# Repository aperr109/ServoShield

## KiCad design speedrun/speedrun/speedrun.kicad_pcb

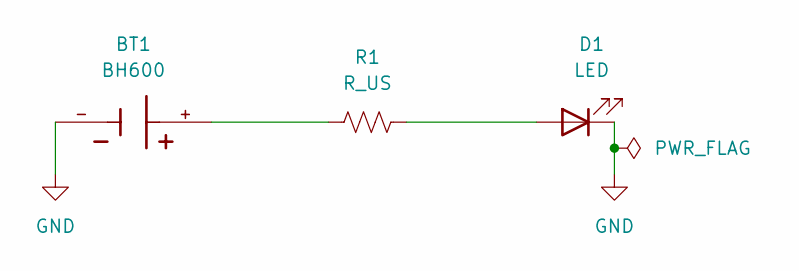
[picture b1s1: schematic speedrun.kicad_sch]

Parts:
BT1: BH600; BAT_BH600; PARTREV D
D1: LED; LED_D1.8mm_W3.3mm_H2.4mm
R1: R_US; R_Axial_DIN0414_L11.9mm_D4.5mm_P15.24mm_Horizontal

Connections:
GND: BT1.-, D1.1 (K)
unnamed: BT1.+, R1.1
unnamed: D1.2 (A), R1.2

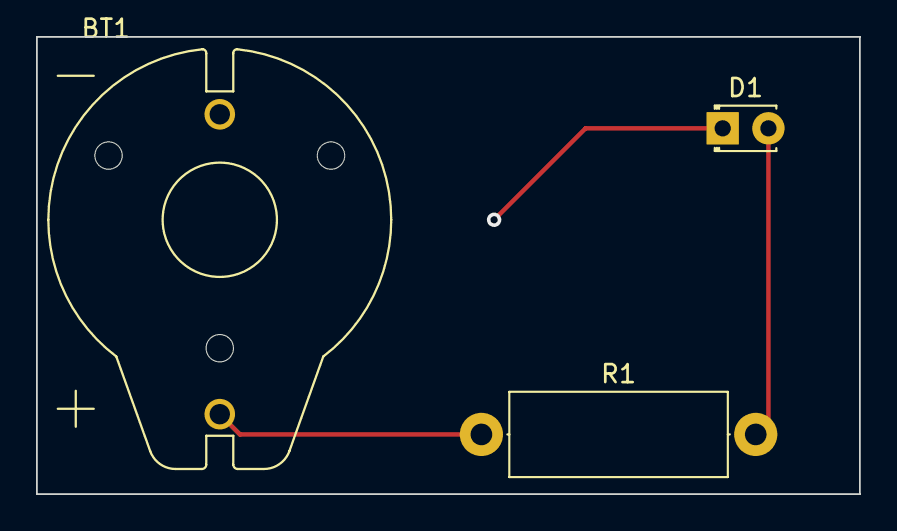
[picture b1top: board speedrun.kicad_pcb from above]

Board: 4 copper layers, 45.7 x 25.4 mm, 3 parts (0 on the bottom side), 3 nets.

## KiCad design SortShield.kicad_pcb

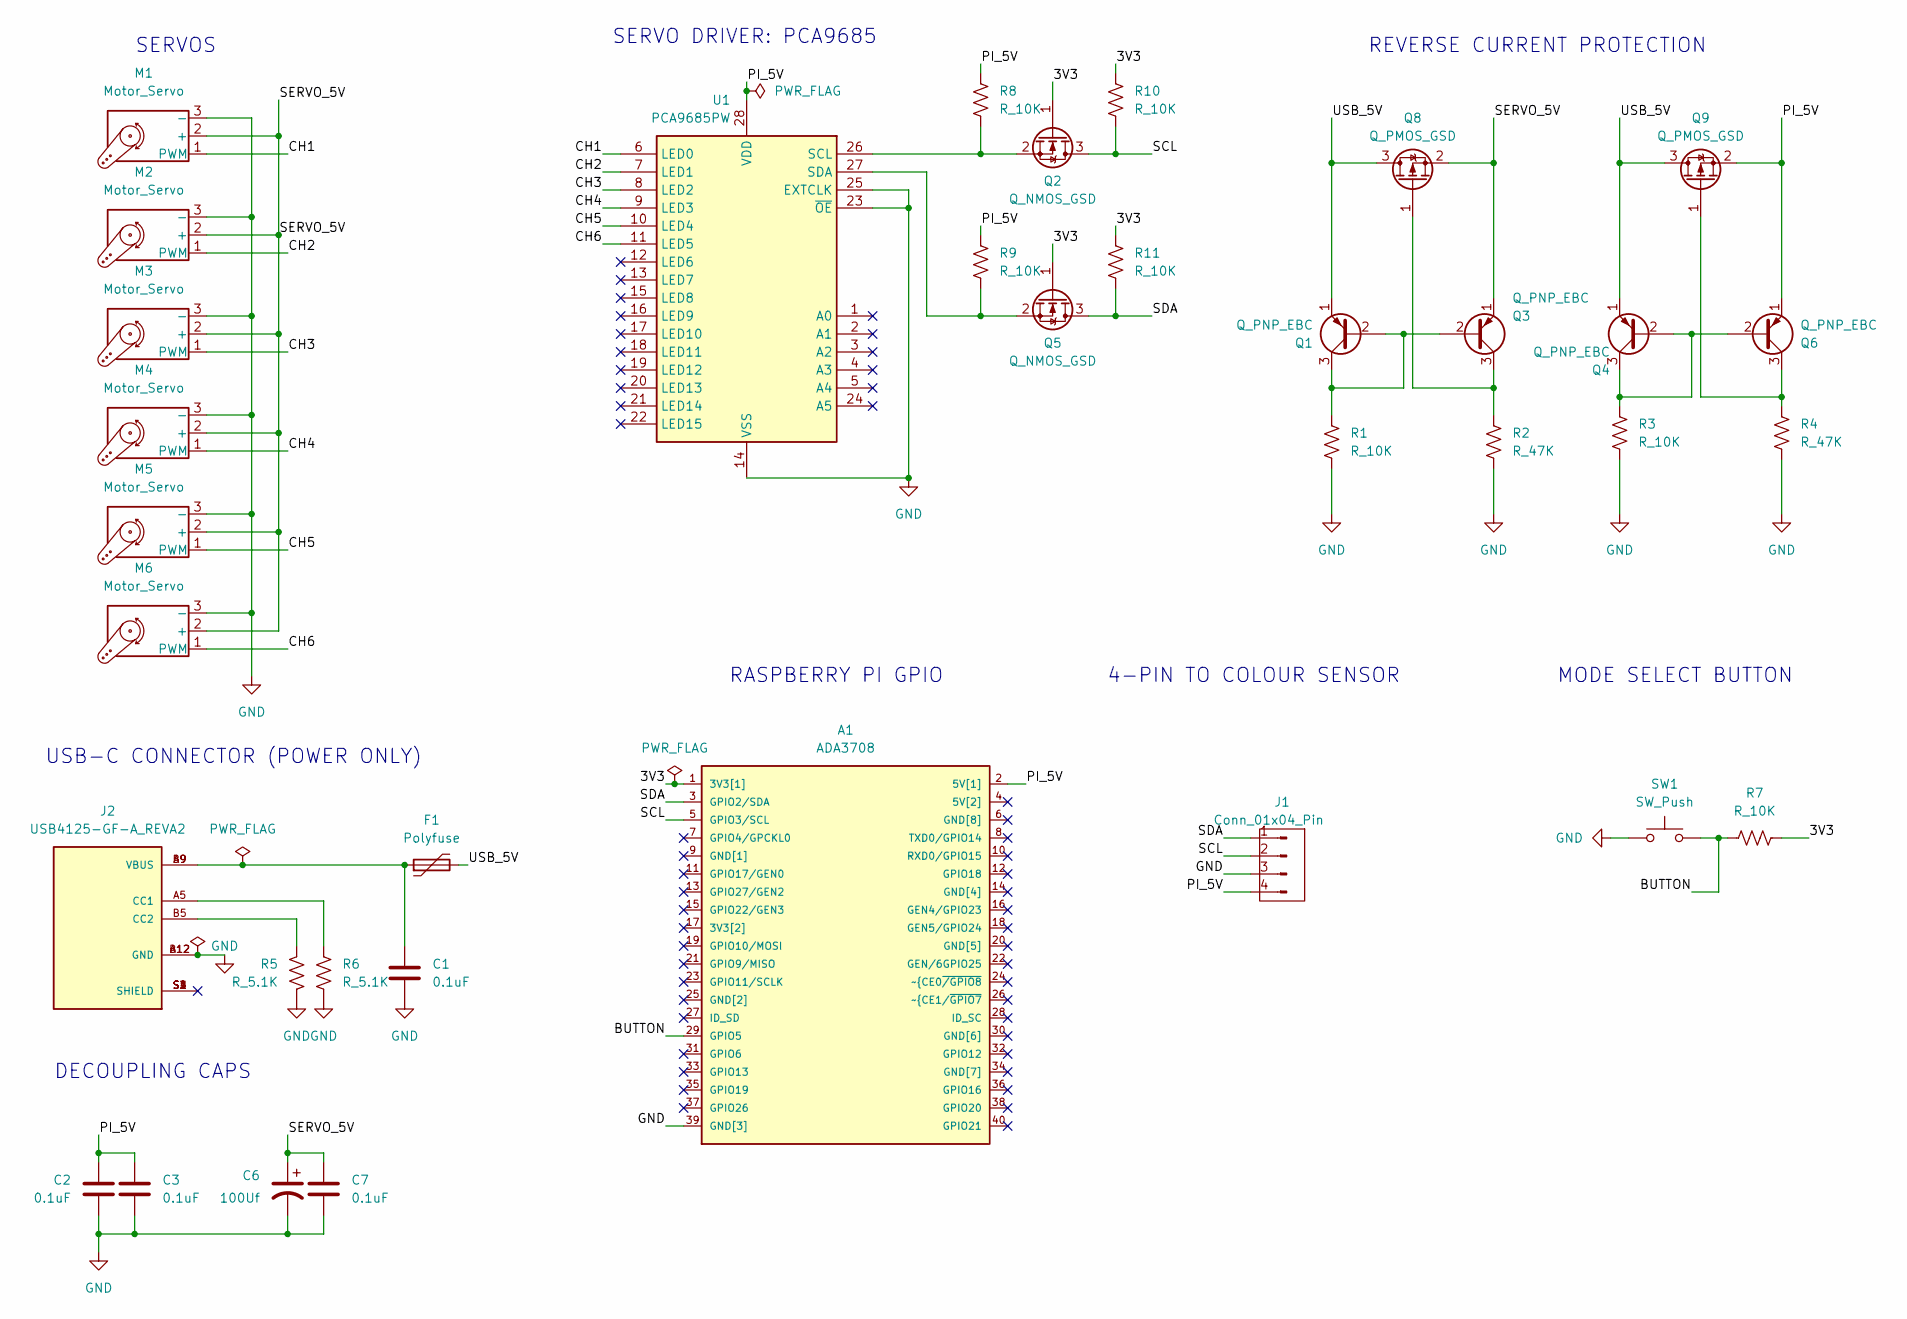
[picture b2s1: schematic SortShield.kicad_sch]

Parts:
A1: ADA3708; ADA3708_RPI-ZERO
C1, C2, C3, C7: 0.1uF; C_0805_2012Metric
C6: 100Uf; CAPAE660X800N
F1: Polyfuse; 6vfuse
J1: Conn_01x04_Pin; PinHeader_1x04_P2.54mm_Vertical
J2: USB4125-GF-A_REVA2; GCT_USB4125-GF-A_REVA2; PARTREV Rev A2
M1, M2, M3, M4, M5, M6: Motor_Servo; PinHeader_1x03_P2.54mm_Vertical
Q1, Q3, Q4, Q6: Q_PNP_EBC; TRANS_MMBT2907A-13
Q2, Q5: Q_NMOS_GSD; SOT91P240X110-3N
Q8, Q9: Q_PMOS_GSD; SSM3J338R,LF
R1, R3, R7, R8, R9, R10, R11: R_10K; R_0805_2012Metric
R2, R4: R_47K; R_0805_2012Metric
R5, R6: R_5.1K; R_0805_2012Metric
SW1: SW_Push; SW_TS04-66-65-BK-160-SMT
U1: PCA9685PW; TSSOP-28_4.4x9.7mm_P0.65mm

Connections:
/3V3: A1.1 (3V3[1]), Q2.1 (G), Q5.1 (G), R7.2, R10.1, R11.1
/BUTTON: A1.29 (GPIO5), R7.1, SW1.2
/CH1: M1.1 (PWM), U1.6 (LED0)
/CH2: M2.1 (PWM), U1.7 (LED1)
/CH3: M3.1 (PWM), U1.8 (LED2)
/CH4: M4.1 (PWM), U1.9 (LED3)
/CH5: M5.1 (PWM), U1.10 (LED4)
/CH6: M6.1 (PWM), U1.11 (LED5)
/PI_5V: A1.2 (5V[1]), C2.1, C3.1, J1.4, Q6.1 (E), Q9.2 (S), R8.1, R9.1, U1.28 (VDD)
/SCL: A1.5 (GPIO3/SCL), J1.2, Q2.3 (D), R10.2
/SDA: A1.3 (GPIO2/SDA), J1.1, Q5.3 (D), R11.2
/SERVO_5V: C6.1, C7.1, M1.2 (+), M2.2 (+), M3.2 (+), M4.2 (+), M5.2 (+), M6.2 (+), Q3.1 (E), Q8.2 (S)
/USB_5V: F1.2, Q1.1 (E), Q4.1 (E), Q8.3 (D), Q9.3 (D)
GND: A1.39 (GND[3]), C1.2, C2.2, C3.2, C6.2, C7.2, J1.3, J2.A12 (GND), J2.B12 (GND), M1.3 (-), M2.3 (-), M3.3 (-), M4.3 (-), M5.3 (-), M6.3 (-), R1.2, R2.2, R3.2, R4.2, R5.2, R6.2, SW1.1, U1.14 (VSS), U1.23 (~OE), U1.25 (EXTCLK)
unnamed: C1.1, F1.1, J2.A9 (VBUS), J2.B9 (VBUS)
unnamed: J2.A5 (CC1), R6.1
unnamed: J2.B5 (CC2), R5.1
unnamed: Q1.2 (B), Q1.3 (C), Q3.2 (B), R1.1
unnamed: Q2.2 (S), R8.2, U1.26 (SCL)
unnamed: Q3.3 (C), Q8.1 (G), R2.1
unnamed: Q4.2 (B), Q4.3 (C), Q6.2 (B), R3.1
unnamed: Q5.2 (S), R9.2, U1.27 (SDA)
unnamed: Q6.3 (C), Q9.1 (G), R4.1

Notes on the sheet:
MODE SELECT BUTTON
SERVO DRIVER: PCA9685
REVERSE CURRENT PROTECTION
RASPBERRY PI GPIO
4-PIN TO COLOUR SENSOR
DECOUPLING CAPS
SERVOS
USB-C CONNECTOR (POWER ONLY)

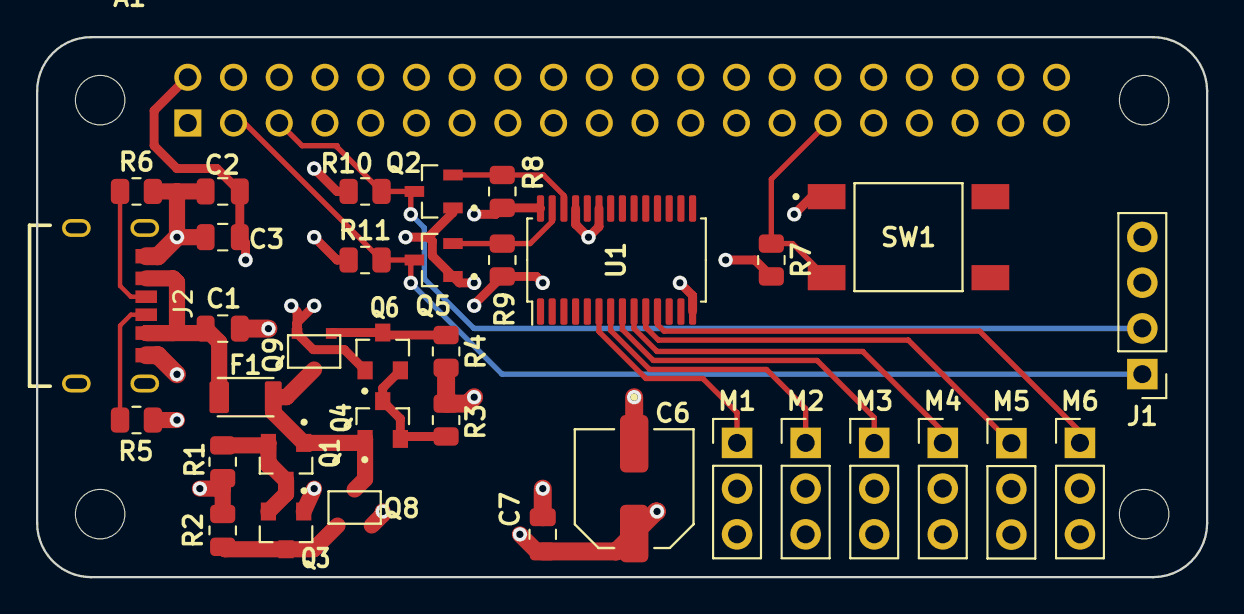
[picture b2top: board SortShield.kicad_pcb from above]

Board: 4 copper layers, 65.0 x 30.0 mm, 36 parts (0 on the bottom side), 23 nets.

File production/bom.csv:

Designator,Footprint,Quantity,Value,LCSC Part #
A1,ADA3708_RPI-ZERO,1,ADA3708,
"C1, C2, C3, C7",0805,4,0.1uF,
C6,CAPAE660X800N,1,100Uf,
F1,6vfuse,1,Polyfuse,
J1,PinHeader_1x04_P2.54mm_Vertical,1,Conn_01x04_Pin,
J2,GCT_USB4125-GF-A_REVA2,1,USB4125-GF-A_REVA2,
"M1, M2, M3, M4, M5, M6",PinHeader_1x03_P2.54mm_Vertical,6,Motor_Servo,
"Q1, Q3, Q4, Q6",TRANS_MMBT2907A-13,4,Q_PNP_EBC,
"Q2, Q5",SOT91P240X110-3N,2,Q_NMOS_GSD,
"Q8, Q9","SSM3J338R,LF",2,Q_PMOS_GSD,
"R1, R10, R11, R3, R7, R8, R9",0805,7,R_10K,
"R2, R4",0805,2,R_47K,
"R5, R6",0805,2,R_5.1K,
SW1,SW_TS04-66-65-BK-160-SMT,1,SW_Push,
U1,TSSOP-28_4.4x9.7mm_P0.65mm,1,PCA9685PW,

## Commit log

2025-07-20 uploaded all current versions of the board files and added proper gitignore
